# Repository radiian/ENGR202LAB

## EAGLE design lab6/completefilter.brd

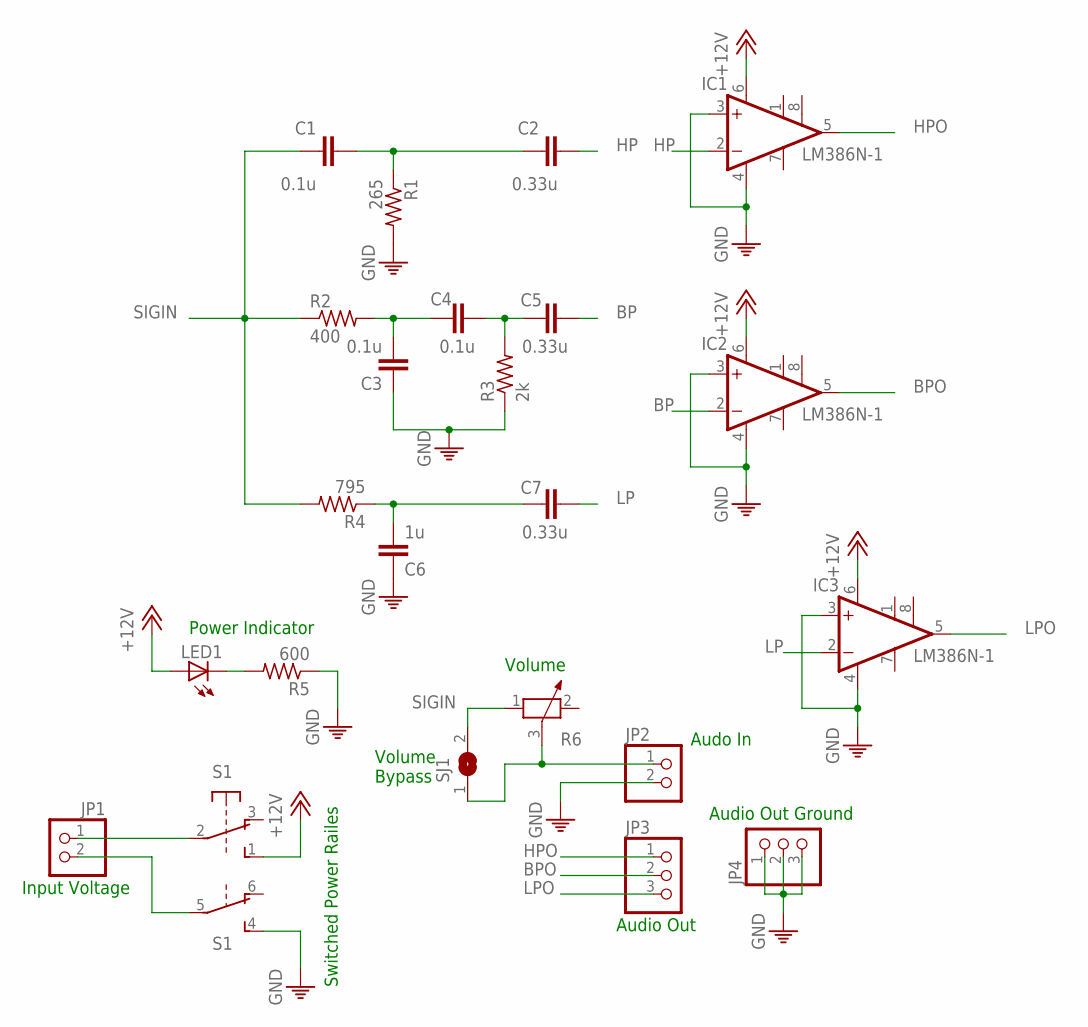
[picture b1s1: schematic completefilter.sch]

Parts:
C1, C3, C4: 0.1u; C1206
C2, C5, C7: 0.33u; C1206
C6: 1u; C1206
IC1, IC2, IC3: LM386N-1; DIL08
JP1, JP2: PINHD-1X2; 1X02
JP3, JP4: PINHD-1X3; 1X03
LED1: LED3MM
R1: 265; R1206
R2: 400; R1206
R3: 2k; R1206
R4: 795; R1206
R5: 600; R1206
R6: POTENTIOMETER_PT-10; PT-10
S1: 9450-2
SJ1: SJW

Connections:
+12V: IC1.6 (VS), IC2.6 (VS), IC3.6 (VS), LED1.A, S1.1 (S)
BP: C5.1, IC2.2 (-IN)
BPO: IC2.5 (OUT), JP3.2
GND: C3.1, C6.1, IC1.3 (+IN), IC1.4 (GND), IC2.3 (+IN), IC2.4 (GND), IC3.3 (+IN), IC3.4 (GND), JP2.2, JP4.1, JP4.2, JP4.3, R1.2, R3.1, R5.1, S1.4 (S)
GNDIN: JP1.2, S1.5
HP: C2.2, IC1.2 (-IN)
HPO: IC1.5 (OUT), JP3.1
LP: C7.1, IC3.2 (-IN)
LPO: IC3.5 (OUT), JP3.3
unnamed: C1.2, C2.1, R1.1
unnamed: C3.2, C4.2, R2.2
unnamed: C4.1, C5.2, R3.2
unnamed: C6.2, C7.2, R4.1
unnamed: LED1.K (C), R5.2
unnamed: JP2.1, R6.3, SJ1.1
SIGIN: C1.1, R2.1, R4.2, R6.1, SJ1.2
VIN: JP1.1, S1.2

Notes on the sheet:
Power Indicator
Input Voltage
Switched Power Railes
Audo In
Volume
Audio Out
Audio Out Ground
Volume Bypass

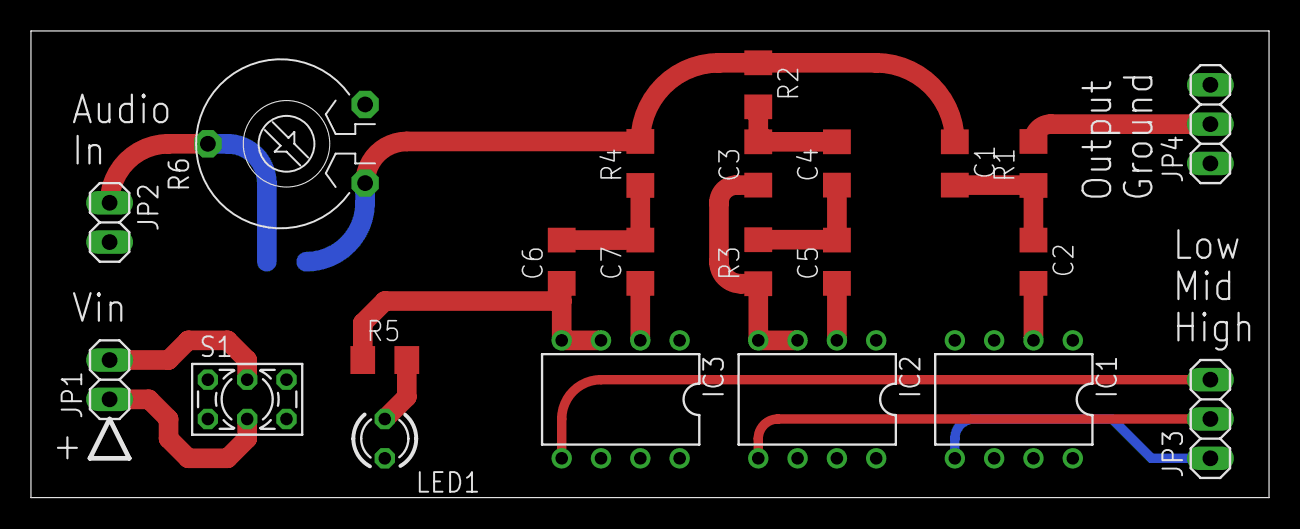
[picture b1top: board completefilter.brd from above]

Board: 2 copper layers, 80.0 x 30.1 mm, 23 parts (1 on the bottom side), 17 nets.

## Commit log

2017-02-12 Repo setup for multi document support. Each lab writeup should now be done in it's own folder given the name of the lab number. A template was added to the root directory for reference.
2017-02-23 Added Simon's work to new repo to bring repo in alignment with old repo
2017-02-23 Compiled current .tex to .pdf
2017-02-23 Re-organization for cleaner work flow. Added templte folder. New labs should be created with: "cp -r template labNumber"
2017-02-23 Added example table for Mercedes Benz. Began work on Tenacious D. On a side note the keyboards here suck ass....
2017-02-23 Began section for Tenacious D as well as added example table. Began work on conclusion section.
2017-02-23 Began work on study questions. Did I mention how terrible this keyboard is? Seriously!
2017-02-23 Changed the title to bold because it looks nicer. Does anyone actually read this shit?
2017-02-23 added data to tables and calculations for tenascious D
2017-02-23 Compiled to pdf. Fuck its early
2017-02-23 finished study questions
2017-02-23 added DC to tables, some formatting
2017-02-23 Ltspice graphs
2017-02-23 added graphs
2017-02-23 files added, compiled
2017-02-23 Setup for lab5
2017-03-01 Began work on Lab 5. Added excel template for tables. Template still needs calculation function setup.
2017-03-02 Add files via upload
    I think I got all the units correct, my handwriting isnt the cleanest so its worth a double check.
2017-03-02 added to the Process
2017-03-02 The three voltage graphs and tables
2017-03-02 Delete Band_Pass_Filter.xlsm
    oops wrong file type
2017-03-02 Delete High_Pass_Filter.xlsm
    oops wrong file type
2017-03-02 Delete Low_Pass_Filter.xlsm
    oops wrong file type
2017-03-02 The correct three filter graphs and tables
    I dont know if we need to graph the phase angles too
2017-03-02 Added to conclusion
2017-03-02 Wrote perl script to convert excel to tex
2017-03-02 added lab data
2017-03-02 Fixed script
2017-03-02 Changed name of perl script to better fit function. Aslo I really really REALLY hate this keyboard.
2017-03-02 Updated perl script to pull more info from csv file
2017-03-02 Created .tex files for each filter table
2017-03-02 compiled
2017-03-02 Added tables from excel
2017-03-02 fixed 100hz voltage
2017-03-02 fixed voltage at 100hz
2017-03-02 Fixed voltage error in high pass table
2017-03-02 added corner frequencies
2017-03-02 formatting
2017-03-02 study question
2017-03-02 compiled shit
2017-03-03 Create new folder
2017-03-03 LtSpice file schmatic
2017-03-16 begin of lab6
2017-03-16 compiled to pdf and finished conclusion
2017-03-16 .log and .aux files added
2017-03-16 Adding schematic of filter network in eagle cad format.
2017-03-16 Added image capture of filter network schematic or "Box Diagram"
2017-03-17 Added schematic for entire project.
2017-03-17 Designed circuit board to accomodate schematic. Basically just showing off now.
2017-03-17 Cleaned up from circuit/board design
2017-03-17 added graphs and spice stuff
2017-03-17 Simulations and Testing
2017-03-17 stuff
